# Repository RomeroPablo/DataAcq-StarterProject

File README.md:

Check out the confluence: 
https://cloud.wikis.utexas.edu/wiki/spaces/LHRSOLAR/pages/157353879/Data+Acquisition+On-boarding+project

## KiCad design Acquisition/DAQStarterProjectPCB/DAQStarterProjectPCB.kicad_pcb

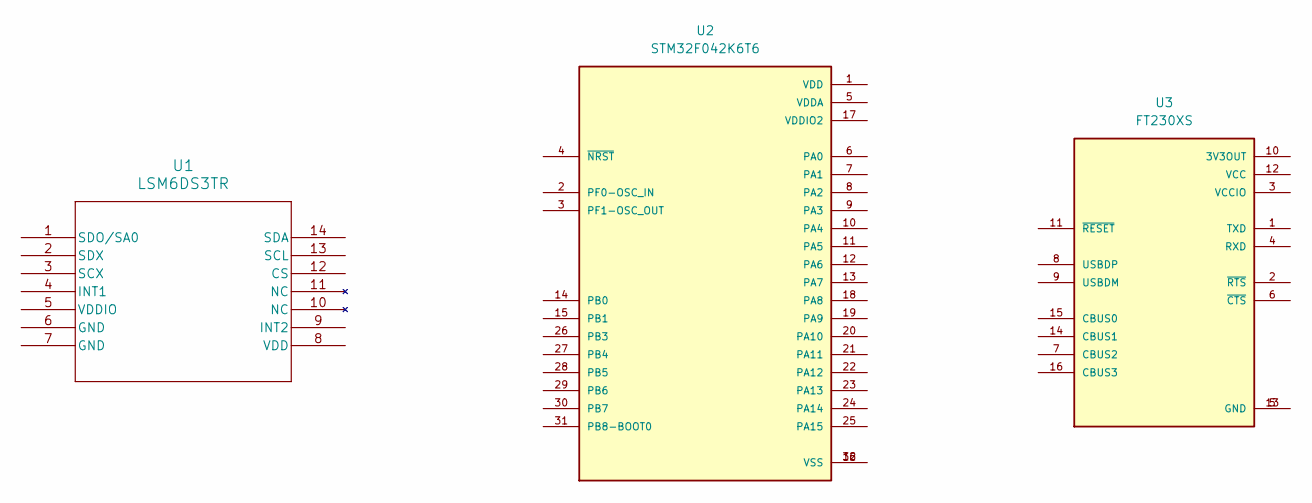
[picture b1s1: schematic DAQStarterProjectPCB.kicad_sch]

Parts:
U1: LSM6DS3TR; LGA-14L_2P5X3X0P83_STM
U2: STM32F042K6T6; QFP80P900X900X160-32N; PARTREV 5
U3: FT230XS; SOP63P599X175-16N; PARTREV 1.5

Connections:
unnamed: U2.16 (VSS), U2.32 (VSS)
unnamed: U3.5 (GND), U3.13 (GND)

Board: 2 copper layers, 3 parts (0 on the bottom side), 2 nets, no tracks yet.

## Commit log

2024-09-27 KiCad + File Structure
2024-09-27 added stm project
2024-09-27 Display Files
2024-09-27 added read pyenv
2024-09-27 added chrono script
2024-09-27 added analysis readme
2024-09-27 add KiCad lib
2024-09-27 added usb sym
2024-09-27 added lsm6 drivers
2024-09-28 Added USB_A Connector
2024-10-05 test1
2024-10-05 rm MCU
2024-10-12 stm-test
2024-10-12 linker
2024-10-12 added lsm6
2024-10-13 refactor
2024-10-19 sampling gyro
2024-10-19 freq
2024-10-19 added bin
